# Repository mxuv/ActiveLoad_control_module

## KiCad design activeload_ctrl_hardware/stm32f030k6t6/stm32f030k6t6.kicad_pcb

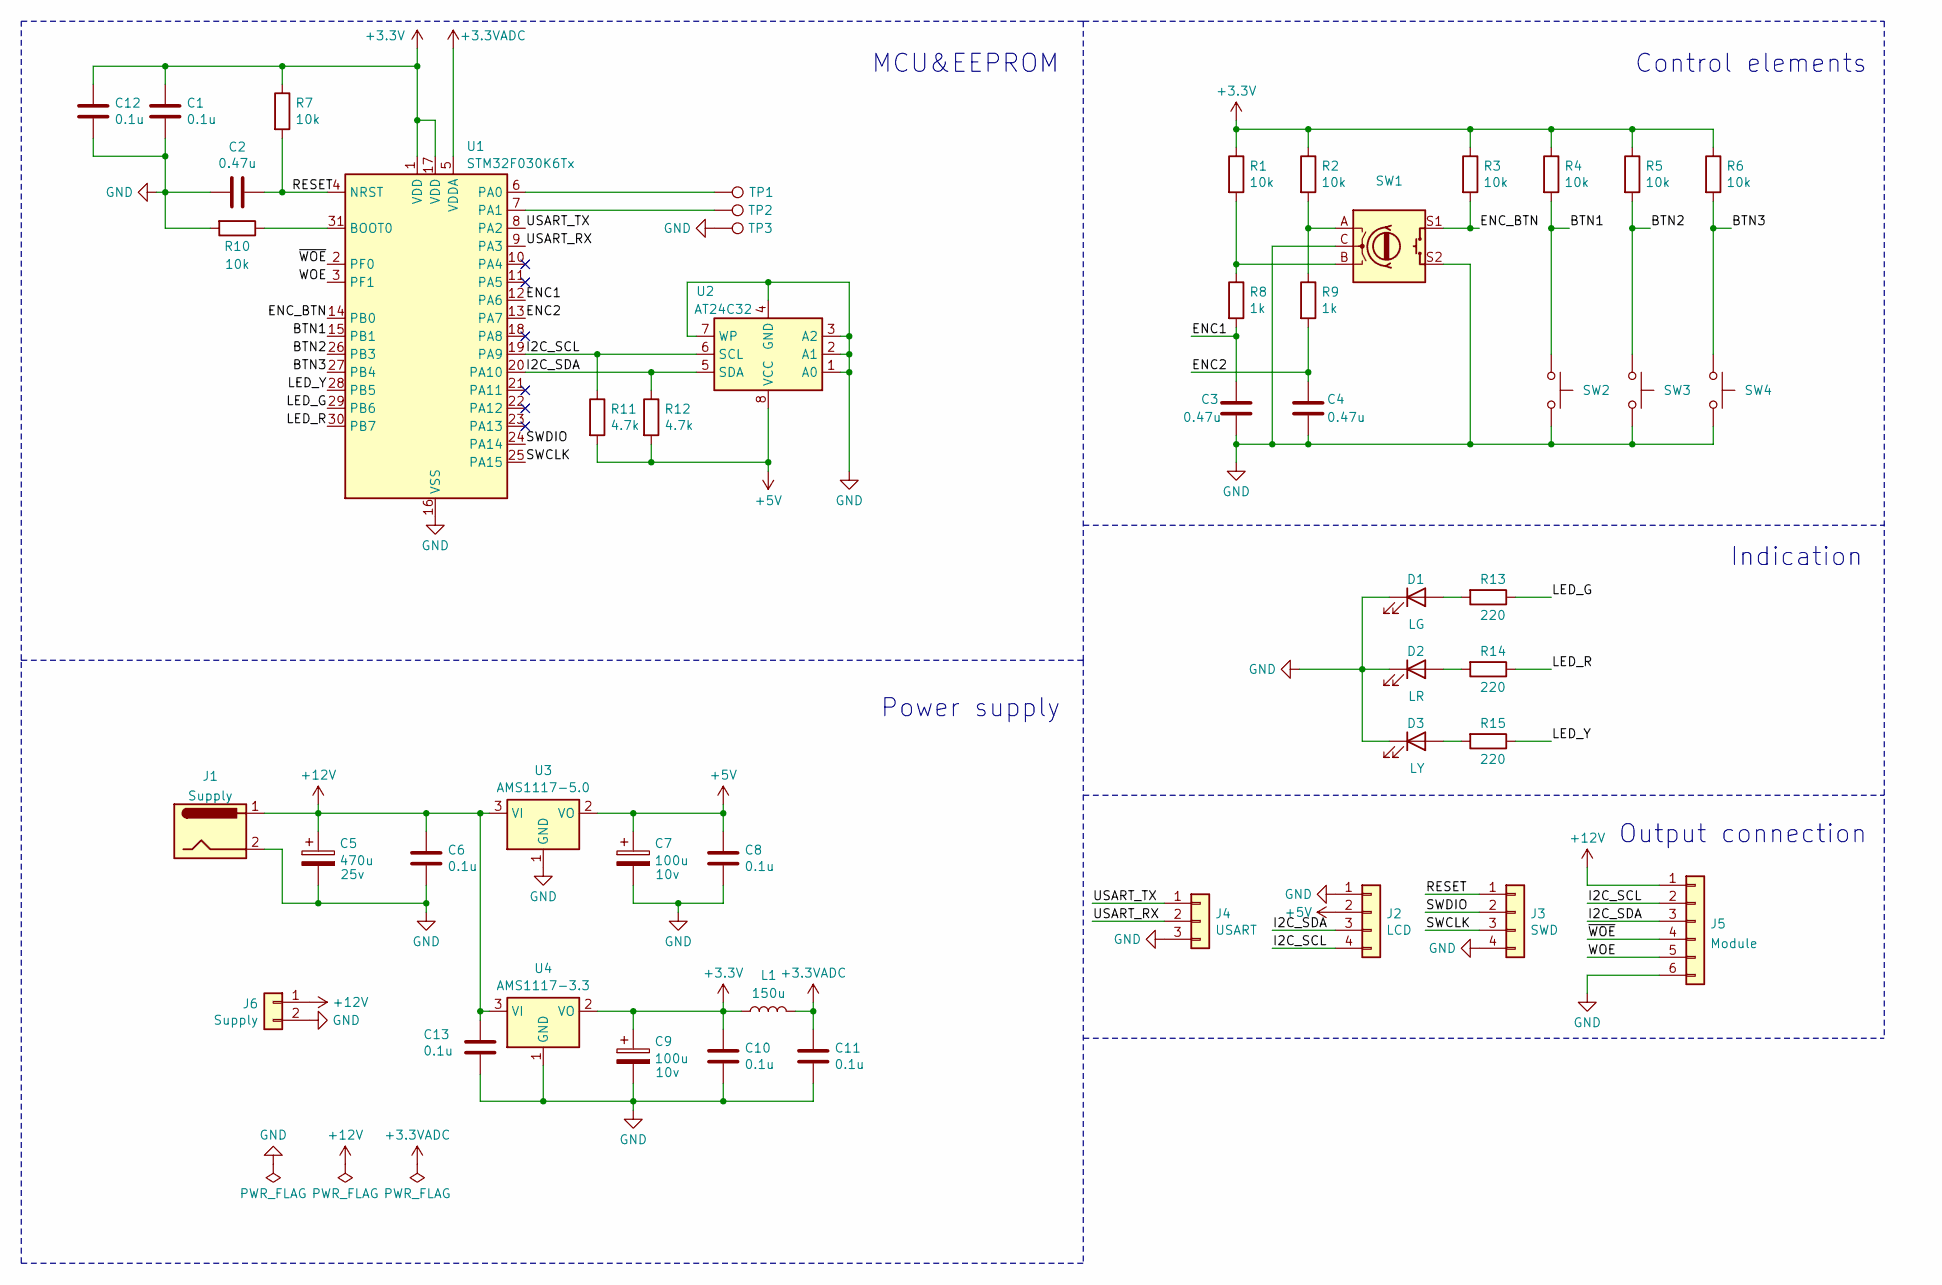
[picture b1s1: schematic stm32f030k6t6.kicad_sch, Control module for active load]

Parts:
C1, C6, C8, C10, C11, C12, C13: 0.1u; C_0805_2012Metric_Pad1.18x1.45mm_HandSolder
C2, C3, C4: 0.47u; C_0805_2012Metric_Pad1.18x1.45mm_HandSolder
C5: 470u; C_Radial_D8.0mm_H7.0mm_P3.50mm; Voltage 25v
C7, C9: 100u; CP_Radial_D4.0mm_P2.00mm; Voltage 10v
D1: LG; LED_1206_3216Metric_Pad1.42x1.75mm_HandSolder
D2: LR; LED_1206_3216Metric_Pad1.42x1.75mm_HandSolder
D3: LY; LED_1206_3216Metric_Pad1.42x1.75mm_HandSolder
J1: Supply; BarrelJack_Horizontal
J2: LCD; PinHeader_1x04_P2.54mm_Vertical
J3: SWD; PinHeader_1x04_P2.54mm_Vertical
J4: USART; PinHeader_1x03_P2.54mm_Vertical
J5: Module; JST_XH_B6B-XH-A_1x06_P2.50mm_Vertical
J6: Supply; TerminalBlock_bornier-2_P5.08mm
L1: 150u; L_1008_2520Metric
R1, R2, R3, R4, R5, R6, R7, R10: 10k; R_1206_3216Metric_Pad1.30x1.75mm_HandSolder
R8, R9: 1k; R_1206_3216Metric_Pad1.30x1.75mm_HandSolder
R11, R12: 4.7k; R_1206_3216Metric_Pad1.30x1.75mm_HandSolder
R13, R14, R15: 220; R_1206_3216Metric_Pad1.30x1.75mm_HandSolder
SW1: RotaryEncoder_Alps_EC12E-Switch_Vertical_H20mm
SW2, SW3, SW4: SW_Push; SW_PUSH-12mm
TP1, TP2, TP3: TestPoint; PinHeader_1x01_P2.54mm_Vertical
U1: STM32F030K6Tx; LQFP-32_7x7mm_P0.8mm
U2: AT24C32; SOIC-8_3.9x4.9mm_P1.27mm
U3: AMS1117-5.0; SOT-223-3_TabPin2
U4: AMS1117-3.3; SOT-223-3_TabPin2

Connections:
+3.3V: C1.1, C9.1, C10.1, C12.1, L1.1, R1.1, R2.1, R3.1, R4.1, R5.1, R6.1, R7.1, U1.1 (VDD), U1.17 (VDD), U4.2 (VO)
+3.3VADC: C11.1, L1.2, U1.5 (VDDA)
+5V: C7.1, C8.1, J2.2, R11.2, R12.2, U2.8 (VCC), U3.2 (VO)
+12V: C5.1, C6.1, C13.1, J1.1, J5.1, J6.1, U3.3 (VI), U4.3 (VI)
/BTN1: R4.2, SW2.1, U1.15 (PB1)
/BTN2: R5.2, SW3.1, U1.26 (PB3)
/BTN3: R6.2, SW4.1, U1.27 (PB4)
/ENC1: C3.1, R8.2, U1.12 (PA6)
/ENC2: C4.1, R9.2, U1.13 (PA7)
/ENC_BTN: R3.2, SW1.S1, U1.14 (PB0)
/I2C_SCL: J2.4, J5.2, R11.1, U1.19 (PA9), U2.6 (SCL)
/I2C_SDA: J2.3, J5.3, R12.1, U1.20 (PA10), U2.5 (SDA)
/LED_G: R13.1, U1.29 (PB6)
/LED_R: R14.1, U1.30 (PB7)
/LED_Y: R15.1, U1.28 (PB5)
/RESET: C2.1, J3.1, R7.2, U1.4 (NRST)
/SWCLK: J3.3, U1.25 (PA15)
/SWDIO: J3.2, U1.24 (PA14)
/USART_RX: J4.2, U1.9 (PA3)
/USART_TX: J4.1, U1.8 (PA2)
/WOE: J5.5, U1.3 (PF1)
/~WOE: J5.4, U1.2 (PF0)
GND: C1.2, C2.2, C3.2, C4.2, C5.2, C6.2, C7.2, C8.2, C9.2, C10.2, C11.2, C12.2, C13.2, D1.1 (K), D2.1 (K), D3.1 (K), J1.2, J2.1, J3.4, J4.3, J5.6, J6.2, R10.2, SW1.C, SW1.S2, SW2.2, SW3.2, SW4.2, TP3.1, U1.16 (VSS), U1.32 (VSS), U2.1 (A0), U2.2 (A1), U2.3 (A2), U2.4 (GND), U2.7 (WP), U3.1 (GND), U4.1 (GND)
unnamed: D1.2 (A), R13.2
unnamed: D2.2 (A), R14.2
unnamed: D3.2 (A), R15.2
unnamed: R1.2, R8.1, SW1.B
unnamed: R2.2, R9.1, SW1.A
unnamed: R10.1, U1.31 (BOOT0)
unnamed: TP1.1, U1.6 (PA0)
unnamed: TP2.1, U1.7 (PA1)

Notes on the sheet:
Control elements
Output connection
MCU&EEPROM
Indication
Power supply

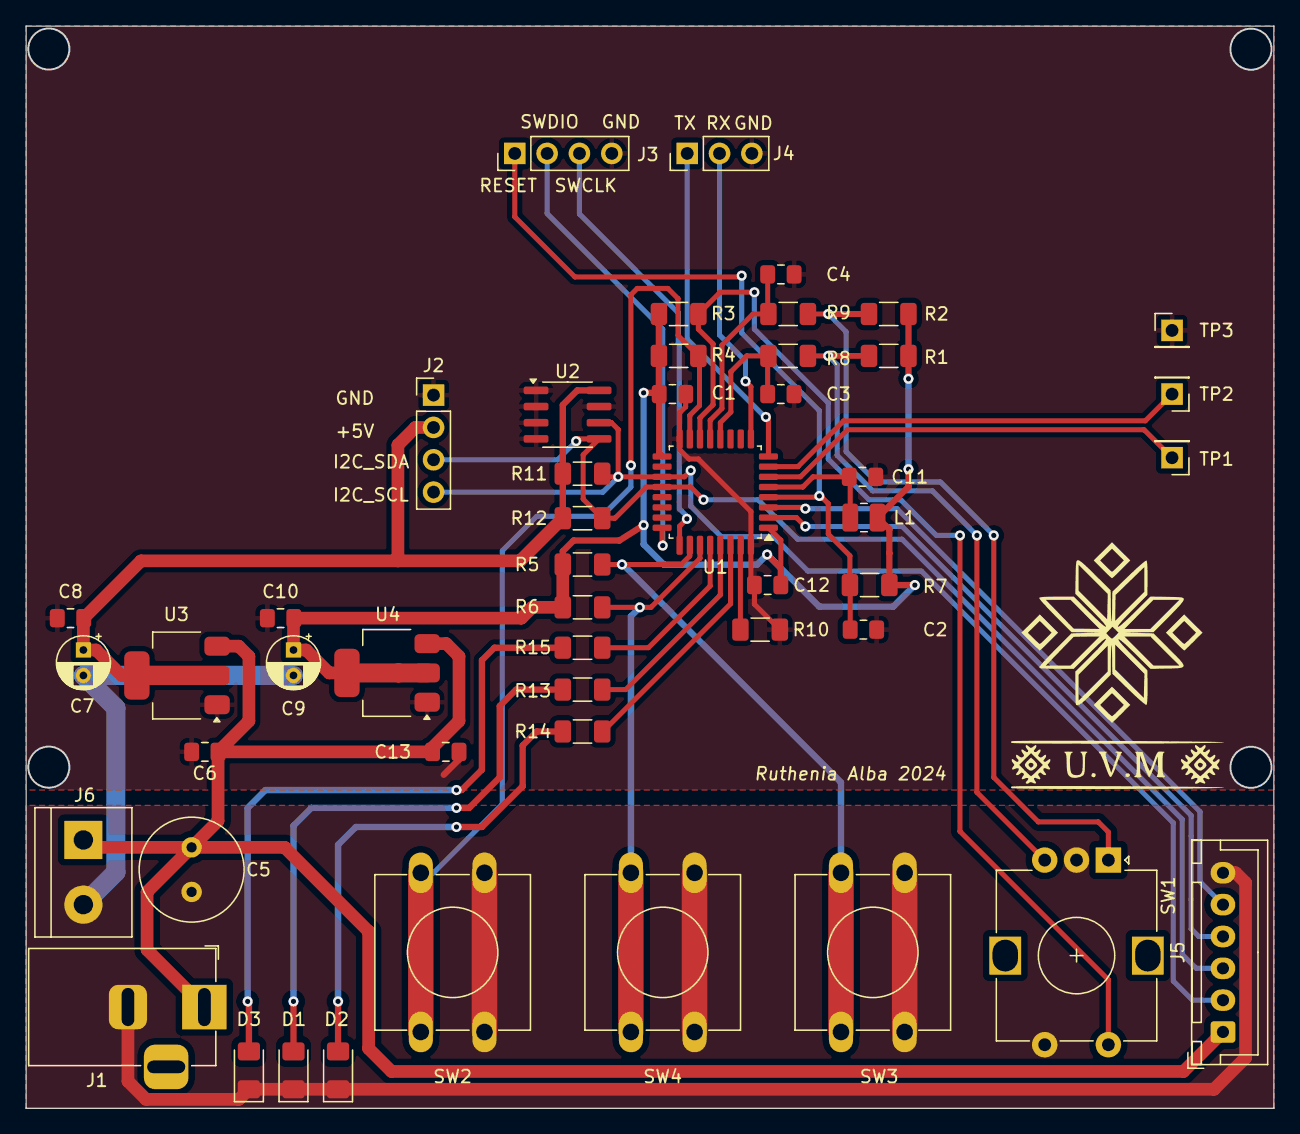
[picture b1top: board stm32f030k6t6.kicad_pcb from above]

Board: 2 copper layers, 98.0 x 84.9 mm, 49 parts (0 on the bottom side), 31 nets.

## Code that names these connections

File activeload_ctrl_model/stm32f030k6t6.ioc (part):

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Mcu.Name=STM32F030K6Tx
Mcu.Package=LQFP32
Mcu.UserName=STM32F030K6Tx
PA10.Mode=I2C
PA10.Signal=I2C1_SDA
PA13.Mode=Serial_Wire
PA13.Signal=SYS_SWDIO
PA14.Mode=Serial_Wire
PA14.Signal=SYS_SWCLK
PA2.Mode=Asynchronous
PA2.Signal=USART1_TX
PA3.Mode=Asynchronous
PA3.Signal=USART1_RX
PA6.Signal=S_TIM3_CH1
PA7.Signal=S_TIM3_CH2
PA9.Mode=I2C
PA9.Signal=I2C1_SCL
PB0.GPIOParameters=GPIO_Label
PB0.GPIO_Label=ENC_BTN
PB0.Signal=GPIO_Input
PB1.GPIOParameters=GPIO_Label
PB1.GPIO_Label=BTN1
PB1.Signal=GPIO_Output
PB3.GPIOParameters=GPIO_Label
PB3.GPIO_Label=BTN2
PB3.Signal=GPIO_Input
PB4.GPIOParameters=GPIO_Label
PB4.GPIO_Label=BTN3
PB4.Signal=GPIO_Input
PB5.GPIOParameters=GPIO_Label
PB5.GPIO_Label=LED_Y
PB5.Signal=GPIO_Output
PB6.GPIOParameters=GPIO_Label
PB6.GPIO_Label=LEG_G
PB6.Signal=GPIO_Output
PB7.GPIOParameters=GPIO_Label
PB7.GPIO_Label=LED_R
PB7.Signal=GPIO_Output
PF0-OSC_IN.GPIOParameters=GPIO_Label
PF0-OSC_IN.GPIO_Label=NWOE
PF0-OSC_IN.Signal=GPIO_Output
PF1-OSC_OUT.GPIOParameters=GPIO_Label
PF1-OSC_OUT.GPIO_Label=WOE
PF1-OSC_OUT.Signal=GPIO_Output
board=custom

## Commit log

2024-08-06 Electrical scheme
2024-08-06 New version for stm32f030k6t6
2024-08-06 PCB start
2024-08-07 PCB processed
2024-08-07 stm32f0k6t6 scheme
2024-08-07 stm32f0f6p6 scheme
2024-08-07 PCB in grogress
2024-08-12 stm32f030k6t6 scheme and model cube mx
2024-08-12 stm32f030k6t6 pcb
2024-08-19 stm32f030k6t6 pcb in grogress
2024-08-20 stm32f030k6t6 gerber files
2024-08-21 stm32f030k6t6 add testpoint to scheme
2024-08-21 stm32f030k6t6 add logo to pcb
2024-08-21 stm32f030k6t6 pdf scheme and ibom.html
